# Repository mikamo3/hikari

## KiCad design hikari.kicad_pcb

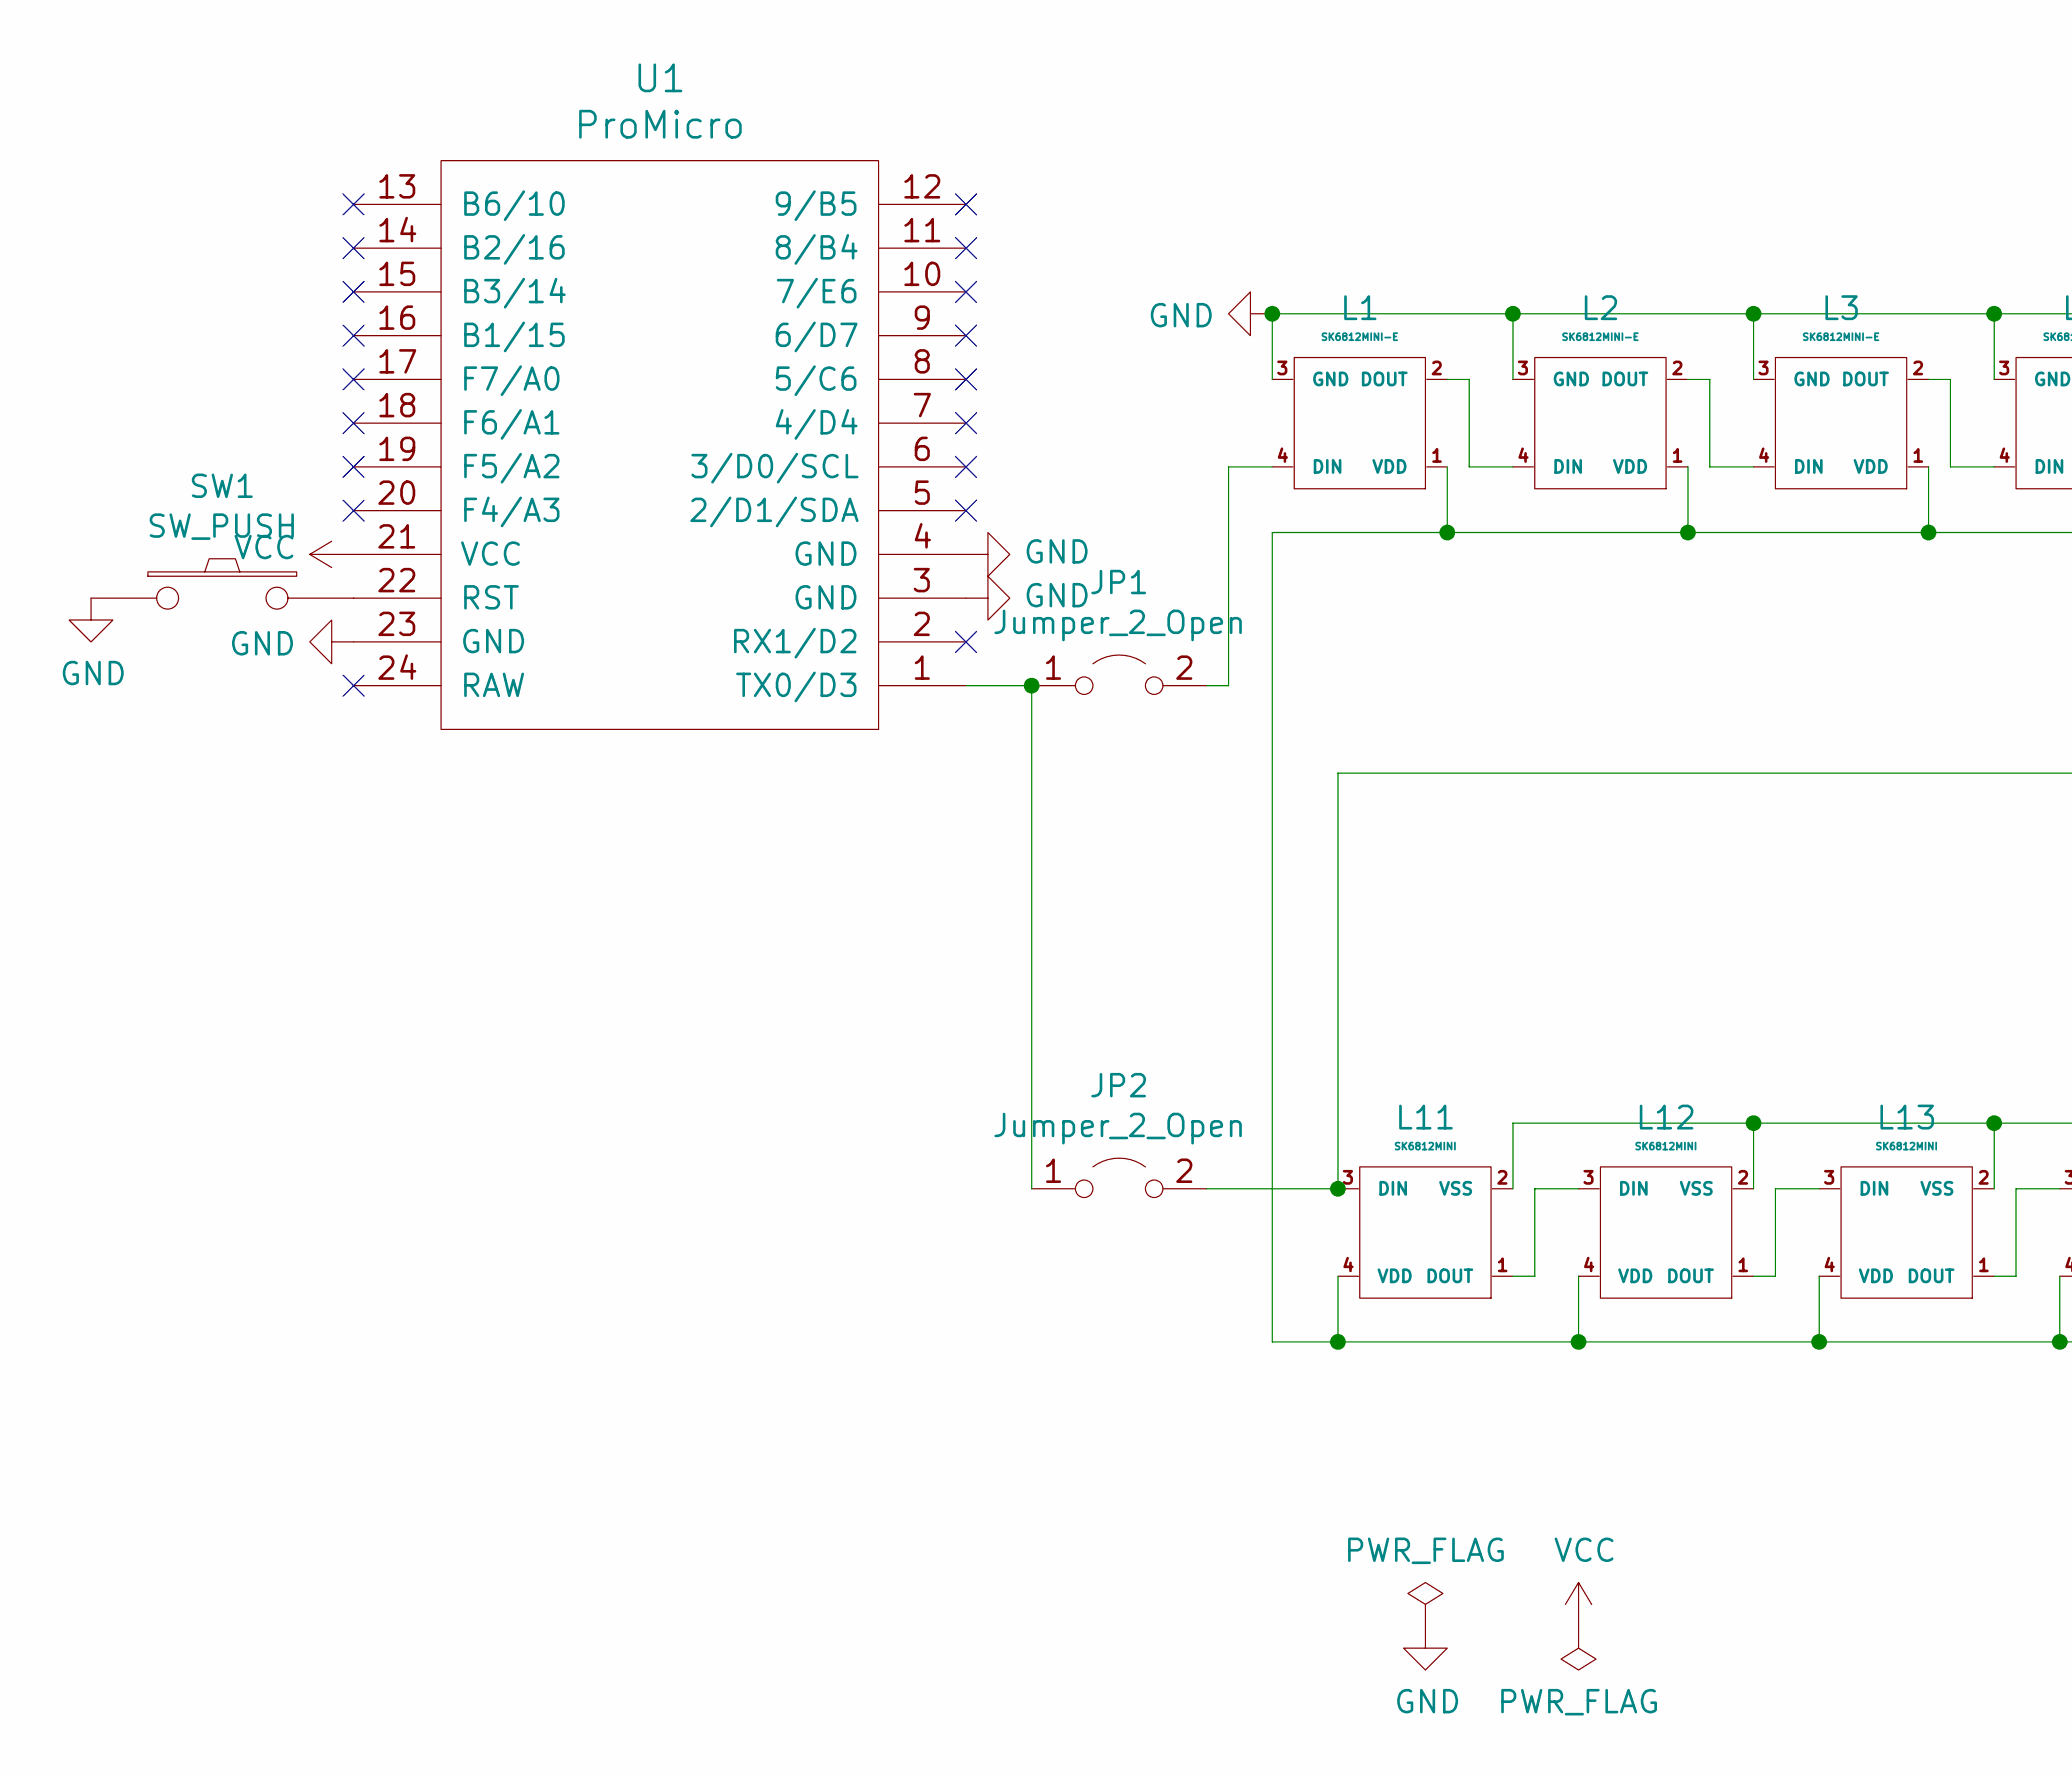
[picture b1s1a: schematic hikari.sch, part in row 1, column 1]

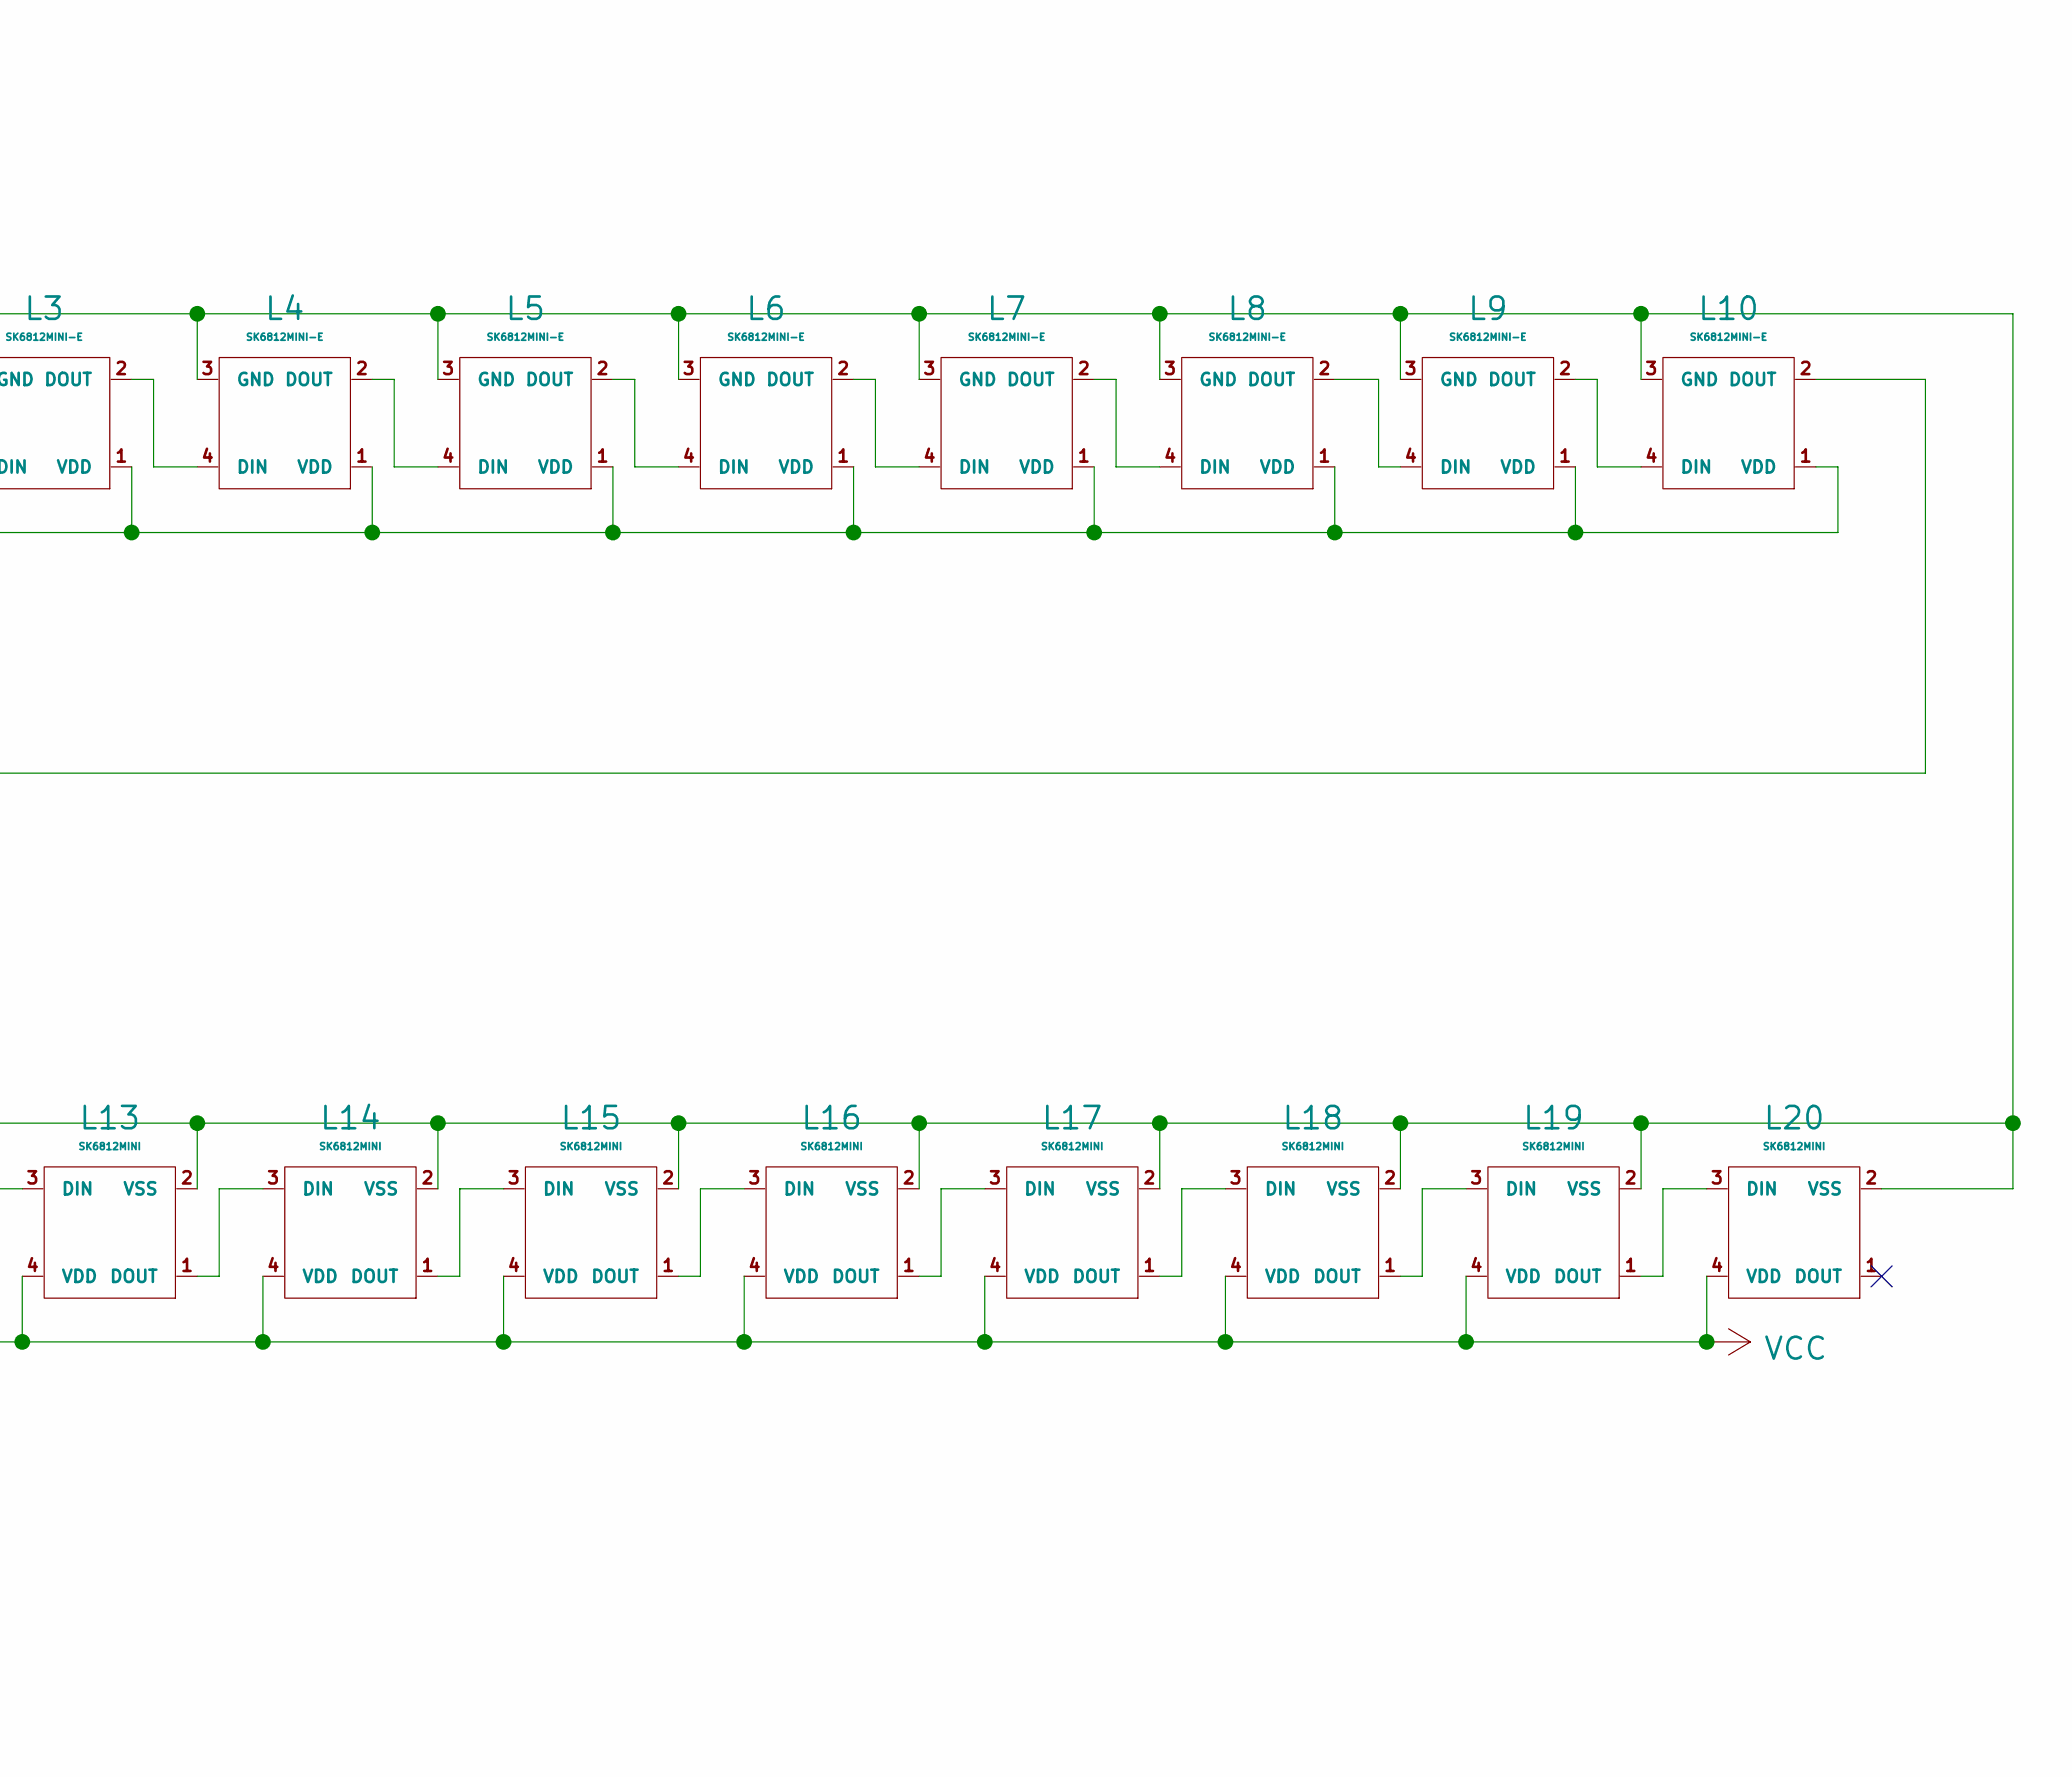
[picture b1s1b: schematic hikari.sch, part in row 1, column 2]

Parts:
JP1, JP2: Jumper_2_Open; Jumper
L1, L2, L3, L4, L5, L6, L7, L8, L9, L10: SK6812MINI-E; YS-SK6812MINI-E
L11, L12, L13, L14, L15, L16, L17, L18, L19, L20: SK6812MINI; SK6812MINI_1side
SW1: SW_PUSH; ResetSW_1side
U1: ProMicro; ProMicro_v3.5

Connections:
GND: L1.3 (GND), L2.3 (GND), L3.3 (GND), L4.3 (GND), L5.3 (GND), L6.3 (GND), L7.3 (GND), L8.3 (GND), L9.3 (GND), L10.3 (GND), L11.2 (VSS), L12.2 (VSS), L13.2 (VSS), L14.2 (VSS), L15.2 (VSS), L16.2 (VSS), L17.2 (VSS), L18.2 (VSS), L19.2 (VSS), L20.2 (VSS), SW1.1, U1.3 (GND), U1.4 (GND), U1.23 (GND)
unnamed: JP1.1 (A), JP2.1 (A), U1.1 (TX0/D3)
unnamed: JP1.2 (B), L1.4 (DIN)
unnamed: JP2.2 (B), L10.2 (DOUT), L11.3 (DIN)
unnamed: L1.2 (DOUT), L2.4 (DIN)
unnamed: L2.2 (DOUT), L3.4 (DIN)
unnamed: L3.2 (DOUT), L4.4 (DIN)
unnamed: L4.2 (DOUT), L5.4 (DIN)
unnamed: L5.2 (DOUT), L6.4 (DIN)
unnamed: L6.2 (DOUT), L7.4 (DIN)
unnamed: L7.2 (DOUT), L8.4 (DIN)
unnamed: L8.2 (DOUT), L9.4 (DIN)
unnamed: L9.2 (DOUT), L10.4 (DIN)
unnamed: L11.1 (DOUT), L12.3 (DIN)
unnamed: L12.1 (DOUT), L13.3 (DIN)
unnamed: L13.1 (DOUT), L14.3 (DIN)
unnamed: L14.1 (DOUT), L15.3 (DIN)
unnamed: L15.1 (DOUT), L16.3 (DIN)
unnamed: L16.1 (DOUT), L17.3 (DIN)
unnamed: L17.1 (DOUT), L18.3 (DIN)
unnamed: L18.1 (DOUT), L19.3 (DIN)
unnamed: L19.1 (DOUT), L20.3 (DIN)
unnamed: SW1.2, U1.22 (RST)
VCC: L1.1 (VDD), L2.1 (VDD), L3.1 (VDD), L4.1 (VDD), L5.1 (VDD), L6.1 (VDD), L7.1 (VDD), L8.1 (VDD), L9.1 (VDD), L10.1 (VDD), L11.4 (VDD), L12.4 (VDD), L13.4 (VDD), L14.4 (VDD), L15.4 (VDD), L16.4 (VDD), L17.4 (VDD), L18.4 (VDD), L19.4 (VDD), L20.4 (VDD), U1.21 (VCC)

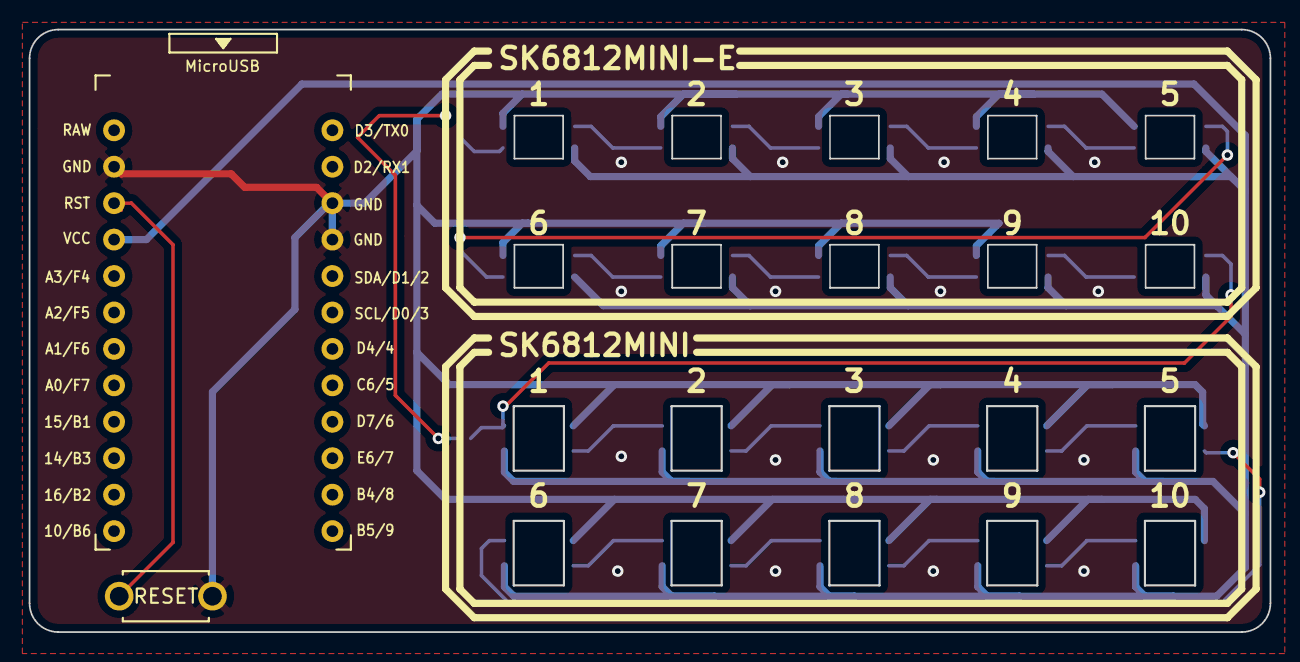
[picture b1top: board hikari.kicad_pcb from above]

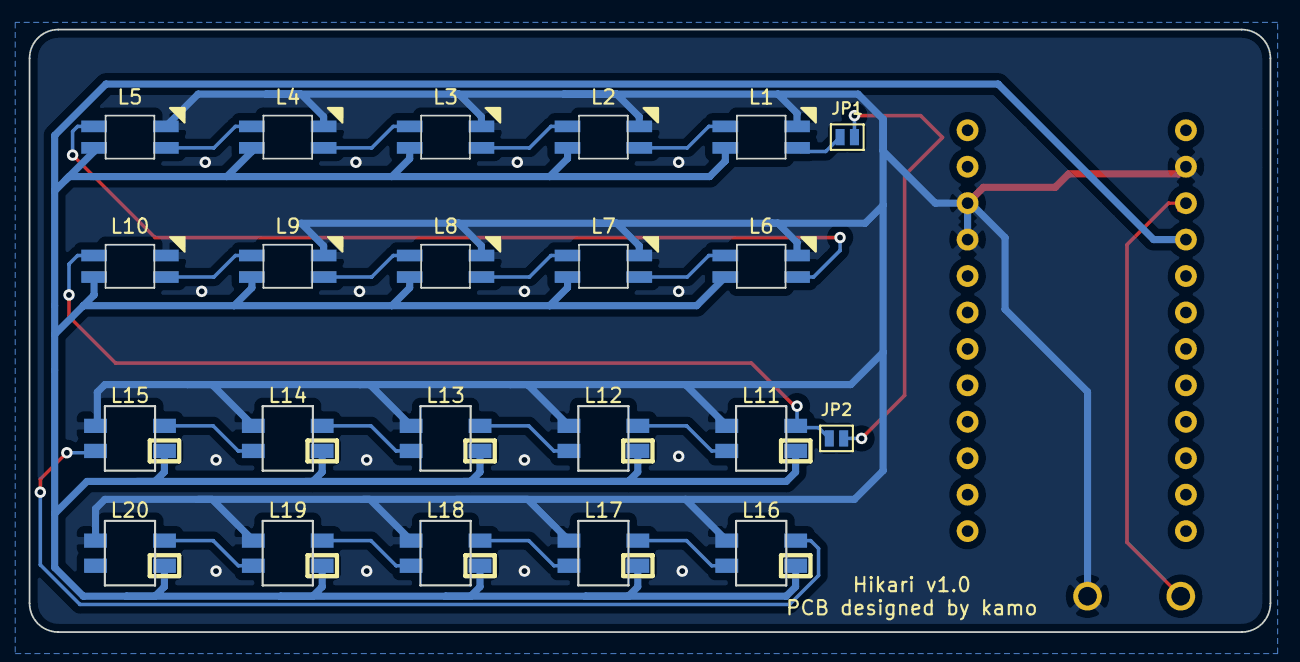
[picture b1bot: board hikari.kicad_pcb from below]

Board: 2 copper layers, 86.5 x 42.0 mm, 24 parts (12 on the bottom side), 24 nets.

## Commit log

2020-12-06 :sparkles: (initialcommit)
2020-12-06 :sparkles: (all) initialcommit
2020-12-11 :sparkles: (pcb) add pcb
2020-12-11 :bug: (remove gerber file)
2021-03-29 :sparkles: (recreate pcb)
2021-03-29 :arrow_up: (lib) update dependency
2021-05-07 :heavy_minus_sign: (all) remove unused dependency
